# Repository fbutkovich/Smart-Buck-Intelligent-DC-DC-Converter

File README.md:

# Smart Buck Intelligent DC-DC Converter
Buck topology voltage converter with power monitoring functionality using the TI INA219 current sense IC.

The provided package includes the source code, necessary dependencies, PCB design, and 3D model files for a buck topology printed circuit board. This PCB is designed to efficiently power various devices, including a dedicated astronomy camera, using a higher voltage lithium-ion battery as the input source. A notable feature of this project design is the inclusion of power monitoring functionality through the utilization of the Texas Instruments INA219 Zero-Drift current/power monitor integrated circuit. The converter's output is a regulated 12 volts DC, capable of delivering up to 3 amperes of current, achieved by employing the Texas Instruments LM2596 SIMPLE SWITCHER 3A Step-Down Voltage Regulator. This configuration proves particularly beneficial when powering a dedicated astrophotography camera with active CMOS sensor cooling. The ability to monitor the camera's power consumption in relation to the fixed temperature setpoint and the surrounding environmental temperature adds significant value to this setup.

The barrel jack style connectors used for the voltage input and output are standard 5.5x2.1mm size, which is very common amongst astronomy equipment and many other consumer electronics.

The embedded firmware for the converter runs on the Microchip SAMD21E17A ARM Cortex M0 microcontroller, and can relay power monitoring statistics to a connected computer over a serial communications port.

The input screw terminal block is intended to be connected to a power tool battery using an “power wheels adapter”, which is fundamentally a flying lead breakout for the voltage of common power tool battery packs (Dewalt, Milwaukee, Makita etc.) that allows replacement of the standard lead-acid battery that comes in most childrens motorized cars.

After the order and assembly of the first revision, as to be expected with any new electronic design there were several mistakes I ended up throubleshooting, thus leading to a few cuts and jumpers on the PCB itself. All of the corrections to the initial design were translated to the current revision of the schematic and layout and include:

* Ground plane disconnected from GND pins of U2, causing numerous headaches when attempting to flash bootloader onto IC and debug.
* Wrong pinout on U6, causing GND to be disconnected and frying IC upon first powerup. STCS05DR symbol and footprint were downloaded directly  from SnapEDA, however it was later discovered they were incorrect for KiCad.
* SWCLK signal needed 1kOhm pullup resistor for the SWD interface to work properly.
* Pinout of reset button was incorrect, again this components (TL3342F160QG) symbol and footprint for KiCad were sourced from SnapEDA, however the symbol led to the ground being connected to pushbutton in the normally     closed position, causing the microcontroller to be in a constant state of reset.
* Footprint size and capacity of feed-forward capacitor required for the LM2596 adjustable buck regulator were incorrect.

# Known Issues
* The onboard 3.3V regulator can be fed from dual voltage supplies, either the USB input, or the 18V battery input. Diodes D1 and D6 (PMEG3015EH) are placed on each voltage rail before tying together at the regulator VIN. After a few uses of the design, it was discovered that D1 had burnt up as the onboard microcontroller would no longer show up in windows as a COM port, and the 3.3V indicator LED would not light up, if an 18V battery was not also connected. The only reason I could think of on why D1 would malfunction would be a higher than rated reverse current due to such a high reverse voltage from the battery input (typically 16-22V) being imposed on the diode, the datasheet specs the reverse current anywhere between 400-1000uA when VR=30V, which is not being exceeded in this use case, however, this also strongly depends on the ambient temperature. I know for a fact that the inside of the enclosure the smart buck PCB is housed in gets considerablly warm when there is a large amount of power draw, which could be what is shortening the lifespan of the diodes. I haven't had time yet to find a suitible replacement diode that will be more robust.

# Project Goal
The primary objective of this project is to develop a compact and high-performance portable power bank that caters specifically to applications requiring 12VDC. The aim is to match the capabilities of commercially available alternatives like the Jackery power station, Celestron PowerTank, and Apertura Portable Telescope Power Supply. Not only does this design excel in size reduction, but it also offers superior performance monitoring and control. By accommodating a variable input DC voltage, which can be sourced from a wide range of commonly available power tool batteries from various manufacturers, the versatility of this power bank is limitless.

I believe the thorough documentation of this electronics project has instilled in me enough confidence to share it with the community as an open-source endeavor. I enthusiastically welcome further contributions to enhance both the hardware design and software implementation. Moreover, I'm open to ideas for additional features and improved functionality, as collaboration and innovation are key factors in driving this project forward.

# License
MIT license

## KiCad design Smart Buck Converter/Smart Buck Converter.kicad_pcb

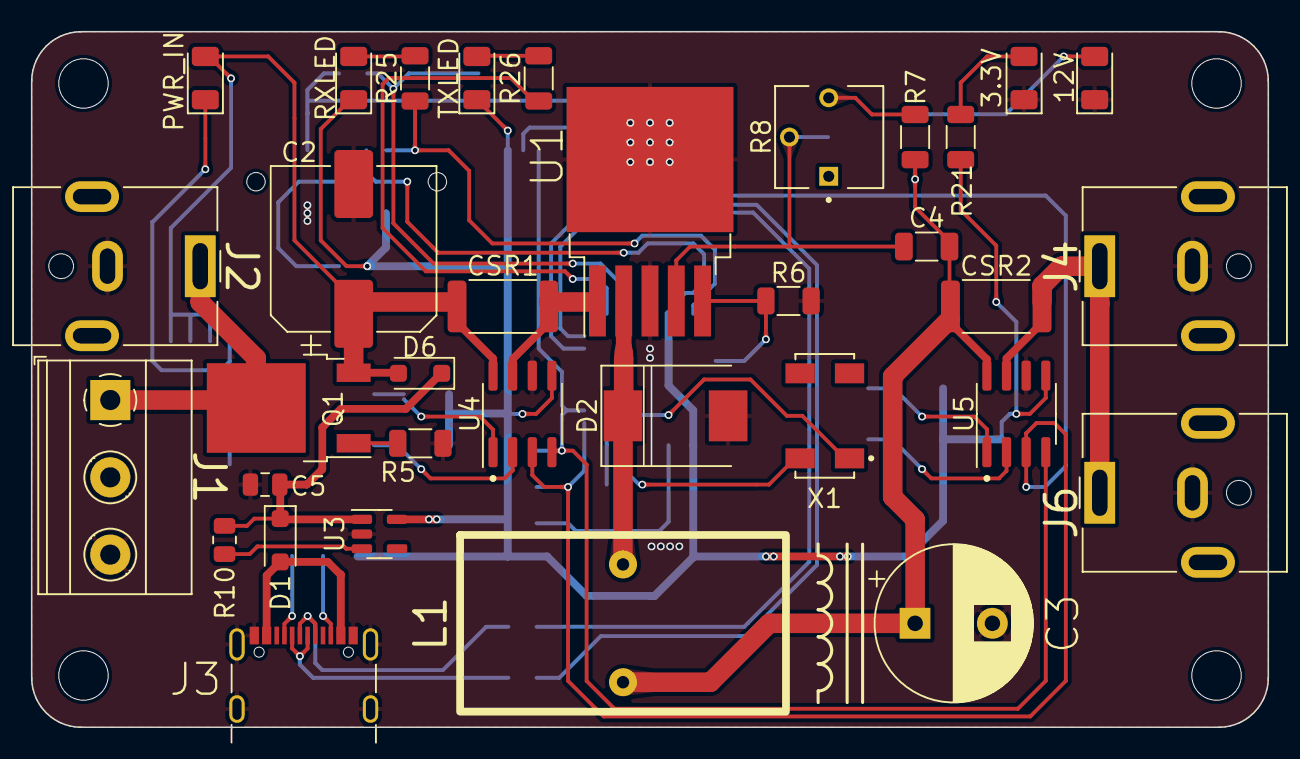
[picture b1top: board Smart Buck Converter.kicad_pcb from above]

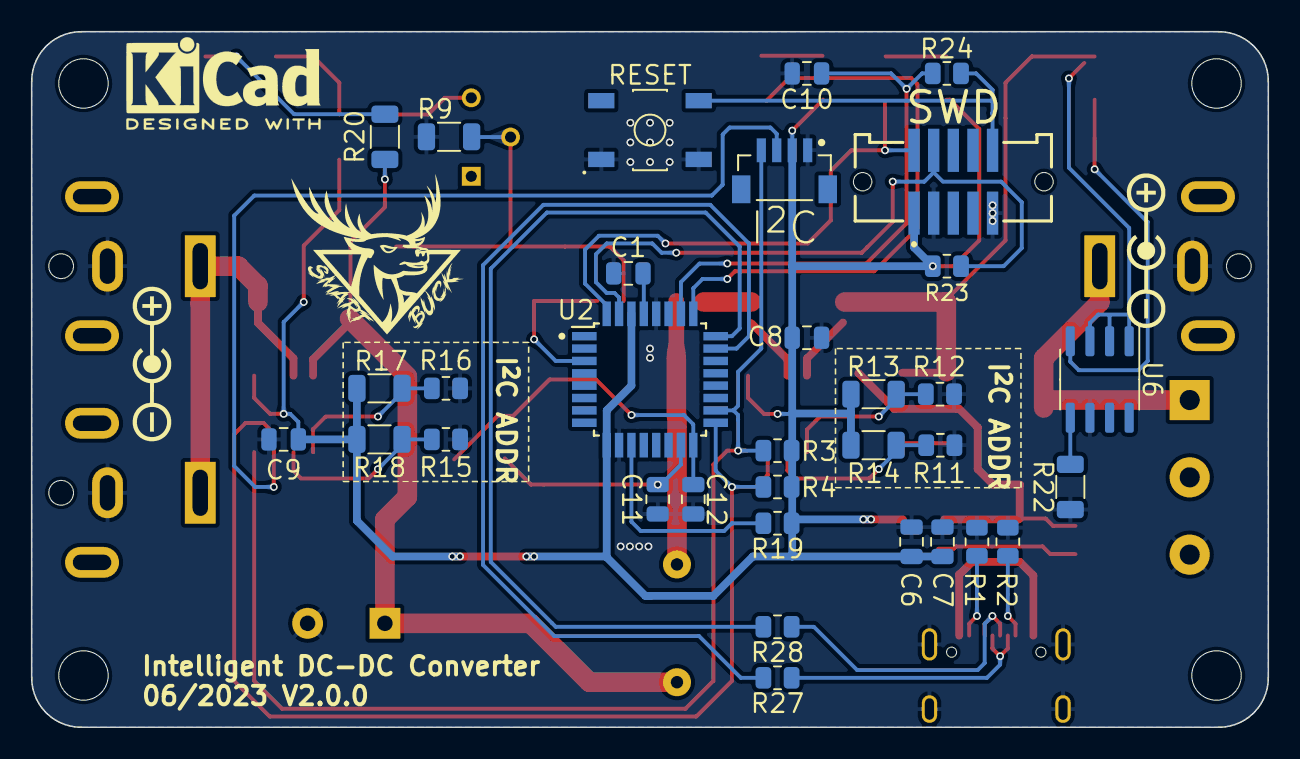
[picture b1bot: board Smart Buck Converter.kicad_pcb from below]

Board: 2 copper layers, 80.0 x 45.0 mm, 67 parts (33 on the bottom side), 40 nets.

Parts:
3.3V: CMD15-21VGD/TR8; LED_1206_3216Metric
12V: CMD15-21VRD/TR8; LED_1206_3216Metric
C1, C7: 1uF; C_0805_2012Metric
C2: 100uF; CP_Elec_10x10.5
C3: 1000uF; CP_Radial_D10.0mm_P5.00mm
C4: 1nF; C_1206_3216Metric
C5, C6: 10uF; C_0805_2012Metric
C8, C9, C10: 0.1uF; C_0805_2012Metric
C11, C12: 22pF; C_0805_2012Metric
CSR1, CSR2: 0.1; R_2512_6332Metric
D1, D6: CDBMHT340-HF; D_SOD-123F
D2: SK33; D_SMC
I^{2}C: SM04B-SRSS-TB(LF)(SN); CONN_BM04B-SRSS-TBT(LF)(SN)
J1: 691101710003; TerminalBlock_Phoenix_MKDS-1,5-3_1x03_P5.00mm_Horizontal
J2, J4, J6: PJ-063AH; BarrelJack_CUI_PJ-063AH_Horizontal
J3: USB4105-GF-A; USB_C_Receptacle_GCT_USB4105-xx-A_16P_TopMnt_Horizontal
L1: PE-54039NL
PWR_IN: CMD15-21VRD/TR8; LED_1206_3216Metric
Q1: IRFR9220TRPBF-BE3; TO-252-2
R1, R2, R19: 5.1k; R_0805_2012Metric
R3, R4, R11, R12, R15, R16: 10.0k; R_0805_2012Metric
R5, R6, R13, R14, R17, R18: 0; R_1206_3216Metric
R7: 8.2k; R_1206_3216Metric
R8: 1.0k; TRIM_3362P-1-103
R9: 1.0k; R_1206_3216Metric
R10: 100k; R_0805_2012Metric
R20: 560; R_1206_3216Metric
R21: 68; R_1206_3216Metric
R22: 5; R_1206_3216Metric
R23: 1.0k; R_0805_2012Metric
R24: 330; R_0805_2012Metric
R25, R26: 1k; R_1206_3216Metric
R27, R28: 0; R_0805_2012Metric
RESET: TL3342F160QG; SW_TL3342F160QG
RXLED: CMD15-21VYC/TR8; LED_1206_3216Metric
SWD: SHF-105-01-L-D-SM; SAMTEC_SHF-105-01-L-D-SM
TXLED: CMD15-21VYC/TR8; LED_1206_3216Metric
U1: LM2596S-ADJ; TO-263-5_TabPin3
U2: ATSAMD21E18A-A; TQFP-32_7x7mm_P0.8mm
U3: AP2204K-3.3; SOT-23-5
U4, U5: INA219AxD; SOIC-8_3.9x4.9mm_P1.27mm
U6: STCS05DR; SOIC-8_3.9x4.9mm_P1.27mm
X1: 830003000; XTAL_ABS25-32.768KHZ-6-1-T

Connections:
+3V3: C6.1, C7.1, C8.1, C9.1, I^{2}C.2, R3.1, R4.1, R13.2, R14.2, R17.2, R18.2, R19.1, R21.1, R23.1, RXLED.1 (K), SWD.01, TXLED.1 (K), U2.9 (VDDANA), U2.30 (VDDIN), U3.5 (VOUT), U4.5 (VS), U5.5 (VS)
/Current Monitoring/PWR_IN_IMON+: C2.1, CSR1.1, D6.2 (A), PWR_IN.2 (A), Q1.3 (S), U4.8 (IN+), U6.1 (V_{CC}), U6.2 (PWM), U6.3 (EN)
/Current Monitoring/PWR_IN_IMON-: CSR1.2, U1.1 (VIN), U4.7 (IN-)
/Current Monitoring/PWR_OUT_IMON+: C3.1, C4.2, CSR2.1, L1.2, R7.2, R20.1, U5.8 (IN+)
/IO Interface/~DEBUG_RST: R24.1, RESET.4, SWD.10
GND: 3.3V.1 (K), 12V.1 (K), C1.1, C2.2, C3.2, C5.2, C6.2, C7.2, C8.2, C9.2, C10.2, C11.1, C12.1, D2.2 (A), I^{2}C.1, J1.3, J2.2, J3.A1 (GND), J3.A12 (GND), J3.B1 (GND), J3.B12 (GND), J3.S1 (SHIELD), J4.2, J6.2, R1.2, R2.2, R5.2, R6.2, R9.2, R11.2, R12.2, R15.2, R16.2, R22.2, RESET.1, RESET.2, SWD.03, SWD.09, U1.3 (GND), U2.10 (GND), U2.28 (GND), U3.2 (GND), U4.6 (GND), U5.6 (GND), U6.6 (GND)
I^{2}C.SCL: I^{2}C.4, R3.2, U2.18 (PA17), U4.4 (SCL), U5.4 (SCL)
I^{2}C.SDA: I^{2}C.3, R4.2, U2.17 (PA16), U4.3 (SDA), U5.3 (SDA)
unnamed: D1.2 (A), J3.A4 (VBUS), J3.A9 (VBUS), J3.B4 (VBUS), J3.B9 (VBUS)
unnamed: D2.1 (K), L1.1, U1.2 (OUT)
unnamed: 12V.2 (A), R20.2
unnamed: 3.3V.2 (A), R21.2
unnamed: PWR_IN.1 (K), U6.4 (DRAIN)
unnamed: J3.A5 (CC1), R2.1
unnamed: J3.B5 (CC2), R1.1
unnamed: Q1.1 (G), R5.1
unnamed: R7.1, R8.3
unnamed: R25.2, RXLED.2 (A)
unnamed: R26.2, TXLED.2 (A)
unnamed: C4.1, R8.2, R9.1, U1.4 (FB)
unnamed: R19.2, U2.11 (PA08)
unnamed: C11.2, U2.15 (PA14), X1.4
unnamed: C12.2, U2.16 (PA15), X1.1
unnamed: C1.2, U2.29 (VDDCORE)
unnamed: R10.2, U3.3 (EN)
unnamed: R11.1, R14.1, U4.2 (A0)
unnamed: R12.1, R13.1, U4.1 (A1)
unnamed: R15.1, R18.1, U5.2 (A0)
unnamed: R16.1, R17.1, U5.1 (A1)
unnamed: R22.1, U6.5 (FB)
PWR_IN: J1.1, J2.1, Q1.2 (D)
PWR_OUT: CSR2.2, J4.1, J6.1, U5.7 (IN-)
RX/SWDIO: R25.1, SWD.02, U2.32 (PA31)
SWCLK: R23.2, SWD.04, U2.31 (PA30)
TX: R26.1, U2.25 (PA27)
USB_D+: J3.A6 (D+), J3.B6 (D+), R28.1
USB_D-: J3.A7 (D-), J3.B7 (D-), R27.1
VBUS: C5.1, D1.1 (K), D6.1 (K), R10.1, U3.1 (VIN)
~BUCK_ENABLE: R6.1, U1.5 (~ON/OFF), U2.3 (PA02)
~RESET: C10.1, R24.2, U2.26 (~RESET)

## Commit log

2023-05-10 Initial commit
    Initial addition of project files. Added description to README.md.
2023-05-10 Added library dependency for INA219
2023-05-10 Created .gitignore
2023-05-10 Modified .gitignore for KiCad extensions
2023-05-10 Added additional image reference in README
2023-05-11 Updated images and README
2023-05-11 Deleted license so it can be changed
2023-05-11 Changed license type to MIT
2023-05-11 Modified image links in README
2023-05-12 Inclusion of KiCad design dependencies
    Added custom components symbols, footprints, and 3D models used for PCB design, all of which will need to be placed in local KiCad directory for PCB design and schematic to be fully editable.
2023-05-12 Changes to README & Design
    Updated revision number of hardware design to 2.0.0, despite the changes for this revision being implemented before this project was version controlled on GitHub. Also regenerated 3D view images of r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
2023-06-07 Revision 2 update
    Regenerated gerber files to rev 2 design, made minor changes to PCB layout before exporting. Changed I2C interface connector from 4-pin right angle style to vertical style, added the new connector th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
2023-12-26 Multiple updates
    Added necessary code to support addition of either 128x64 or 128x32 OLED display from Adafruit. Fixed backwards polarity on RX/TX indicator LEDs. Updated enclosure to support addition of OLED display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
